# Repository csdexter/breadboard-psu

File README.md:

#Breadboard PSU#

(C) 2015 Radu - Eosif Mihailescu <radu.mihailescu@linux360.ro>

All files in this repository are licensed under the
**GNU Generic Public License v3**, a copy of whose text can be accessed
 [here](http://www.gnu.org/licenses/gpl.html).

This repository contains [EDA](http://en.wikipedia.org/wiki/Electronic_design_automation) source files for all of the boards in this project in CadSoft Eagle 7 format. Only the `.SCH` (schematic) and `.BRD` (board) files are provided as all data needed for manufacturing can easily be derived from the former. No guarantee is made as to which minor version of Eagle was used to save the file, but it *may* be the latest at the time of this writing.

The board description files *may* contain routing information or be supplied unrouted. In the former case, the routing artwork *may* have been generated by either Eagle's internal autorouter or [FreeRouting](http://www.freerouting.net/). A 25mil routing grid and 10/10mil trace/space settings will have been used in both cases.

All files included here are compatible with the free version of Eagle (i.e. describe PCBs having no more than 2 layers and measuring no more than 10cm by 8cm each).

Git tags will be used to mark specific revisions that were actually manufactured so that a correspondence between the evolution of the sources and the status of physical by-products can be maintained.

##WARNING##
*Unless and until explictily noted otherwise, the engineering materials here are laboratory quality and neither intended for manufacturing in production quantities nor for distribution (e.g. as kits) to end-users. The design data here does not explicitly follow any widely-accepted safety/security/EMI regulation or standard, therefore any manufacturing and/or usage in connection with live equipment is entirely at your own risk.*

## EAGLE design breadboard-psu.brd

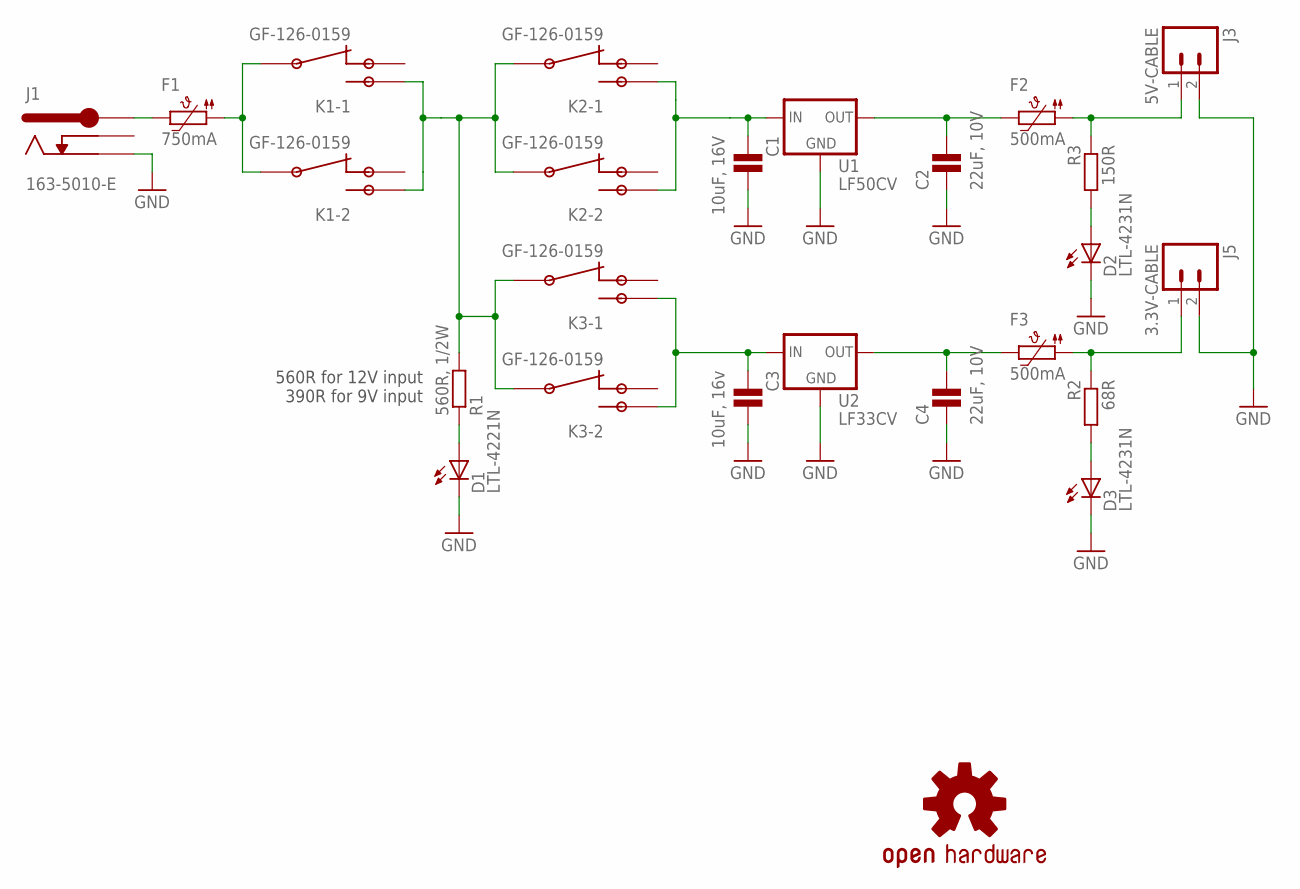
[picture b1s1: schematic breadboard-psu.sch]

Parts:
C1: 10uF, 16V; FK26*
C2, C4: 22uF, 10V; FK20*
C3: 10uF, 16v; FK26*
D1: LTL-4221N; LED3MM
D2, D3: LTL-4231N; LED3MM
F1: 750mA; AXIAL__GENERIC_10X3
F2, F3: 500mA; AXIAL__GENERIC_10X3
J1: 163-5010-E; 163-501*-E
J3: 5V-CABLE; MOLEX-1X2
J5: 3.3V-CABLE; MOLEX-1X2
K1, K2, K3: GF-126-0159
LOGO2: OSHW-LOGOL; OSHW-LOGO-L
R1: 560R, 1/2W; 0204V
R2: 68R; 0204V
R3: 150R; 0204V
U1: LF50CV; TO220-IGO
U2: LF33CV; TO220-IGO

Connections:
3V3: F3.P$1 (1), J5.1, R2.1
5V: F2.P$1 (1), J3.1, R3.1
GND: C1.P$2, C2.P$1, C3.P$2, C4.P$1, D1.K (C), D2.K (C), D3.K (C), J1.P$1 (-), J3.2, J5.2, U1.GND, U2.GND
unnamed: F1.P$2 (2), J1.P$4 (+)
unnamed: F1.P$1 (1), K1.P$2, K1.P$5
unnamed: K1.P$3, K1.P$6, K2.P$2, K2.P$5, K3.P$2, K3.P$5, R1.2
unnamed: C1.P$1, K2.P$3, K2.P$6, U1.IN
unnamed: C3.P$1, K3.P$3, K3.P$6, U2.IN
unnamed: C2.P$2, F2.P$2 (2), U1.OUT
unnamed: C4.P$2, F3.P$2 (2), U2.OUT
unnamed: D1.A, R1.1
unnamed: D2.A, R3.2
unnamed: D3.A, R2.2

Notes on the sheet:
560R for 12V input 390R for 9V input

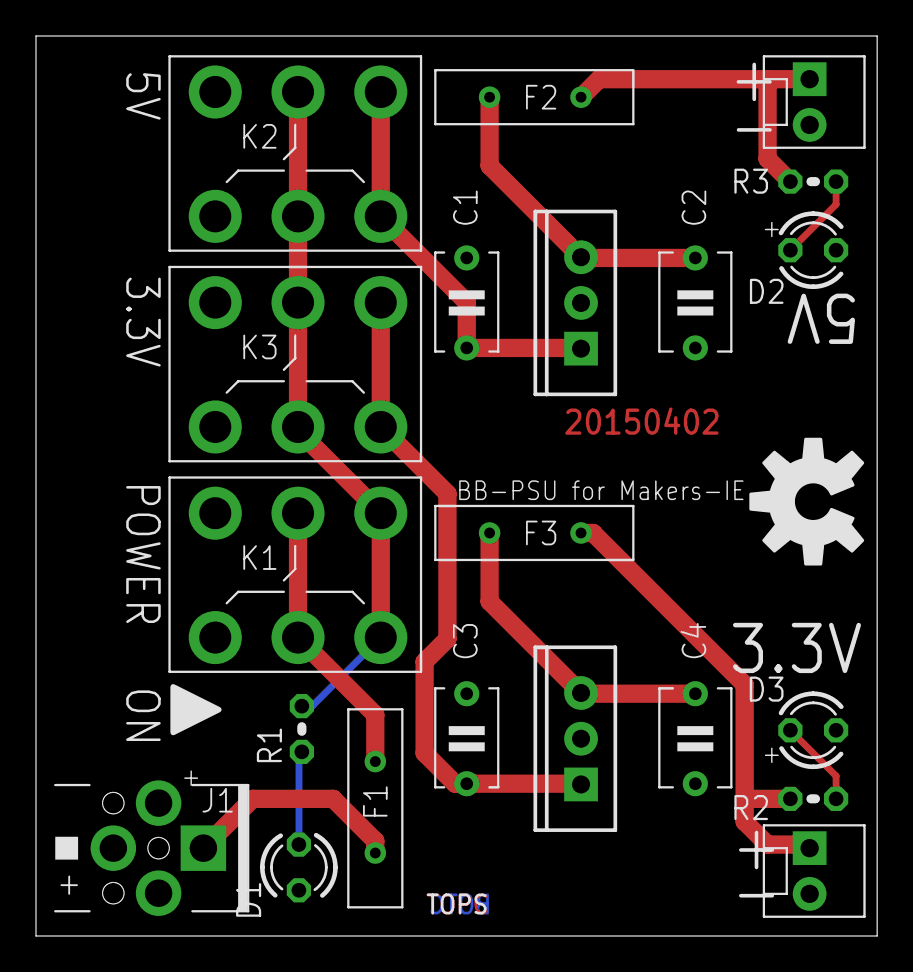
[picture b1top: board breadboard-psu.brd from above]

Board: 2 copper layers, 46.7 x 50.0 mm, 22 parts (0 on the bottom side), 13 nets.

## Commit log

2015-02-21 Initial commit: - SCH and BRD in Eagle 7 - distance between fangs not proven yet, educated guess used - PCB is not finalized, still missing some footprints
2015-02-21 UPDATE: - first draft, schematic is stable, layout is routed and poured. - still left to do the silkscreen and confirm width (to match breadboard). - all footprints checked or generated in-situ to ma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
2015-02-23 UPDATE: - redesigned without fangs as various breadboards have various widths, leaving just cable version in - this allows us to fit in 5x5cm with drastic reduction in price
2015-02-24 Removed redundant subtitle from README
2015-02-24 UPDATE: - PCB done, including silk, aesthetics, physicals and design for manufacturing - this is ready to go to the fab.
2015-02-25 UPDATE: - forgot to put OSHW logo in schematic in the frame documentation box, where it belongs - added gerbv project file to aid offline viewing of manufacturing data - added Eagle3D custom mapping 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
2015-04-02 Adjustments after the trial fab run: - enlarged in X dimension, still fits in 5x5cm - moved power LED behind DC jack, better contrast and visibility - enlarged legend text for switches and added sign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

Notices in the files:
parts and their libraries:
SparkFun-PowerIC: Licensing: Creative Commons ShareAlike 4.0 International - https://creativecommons.org/licenses/by-sa/4.0
